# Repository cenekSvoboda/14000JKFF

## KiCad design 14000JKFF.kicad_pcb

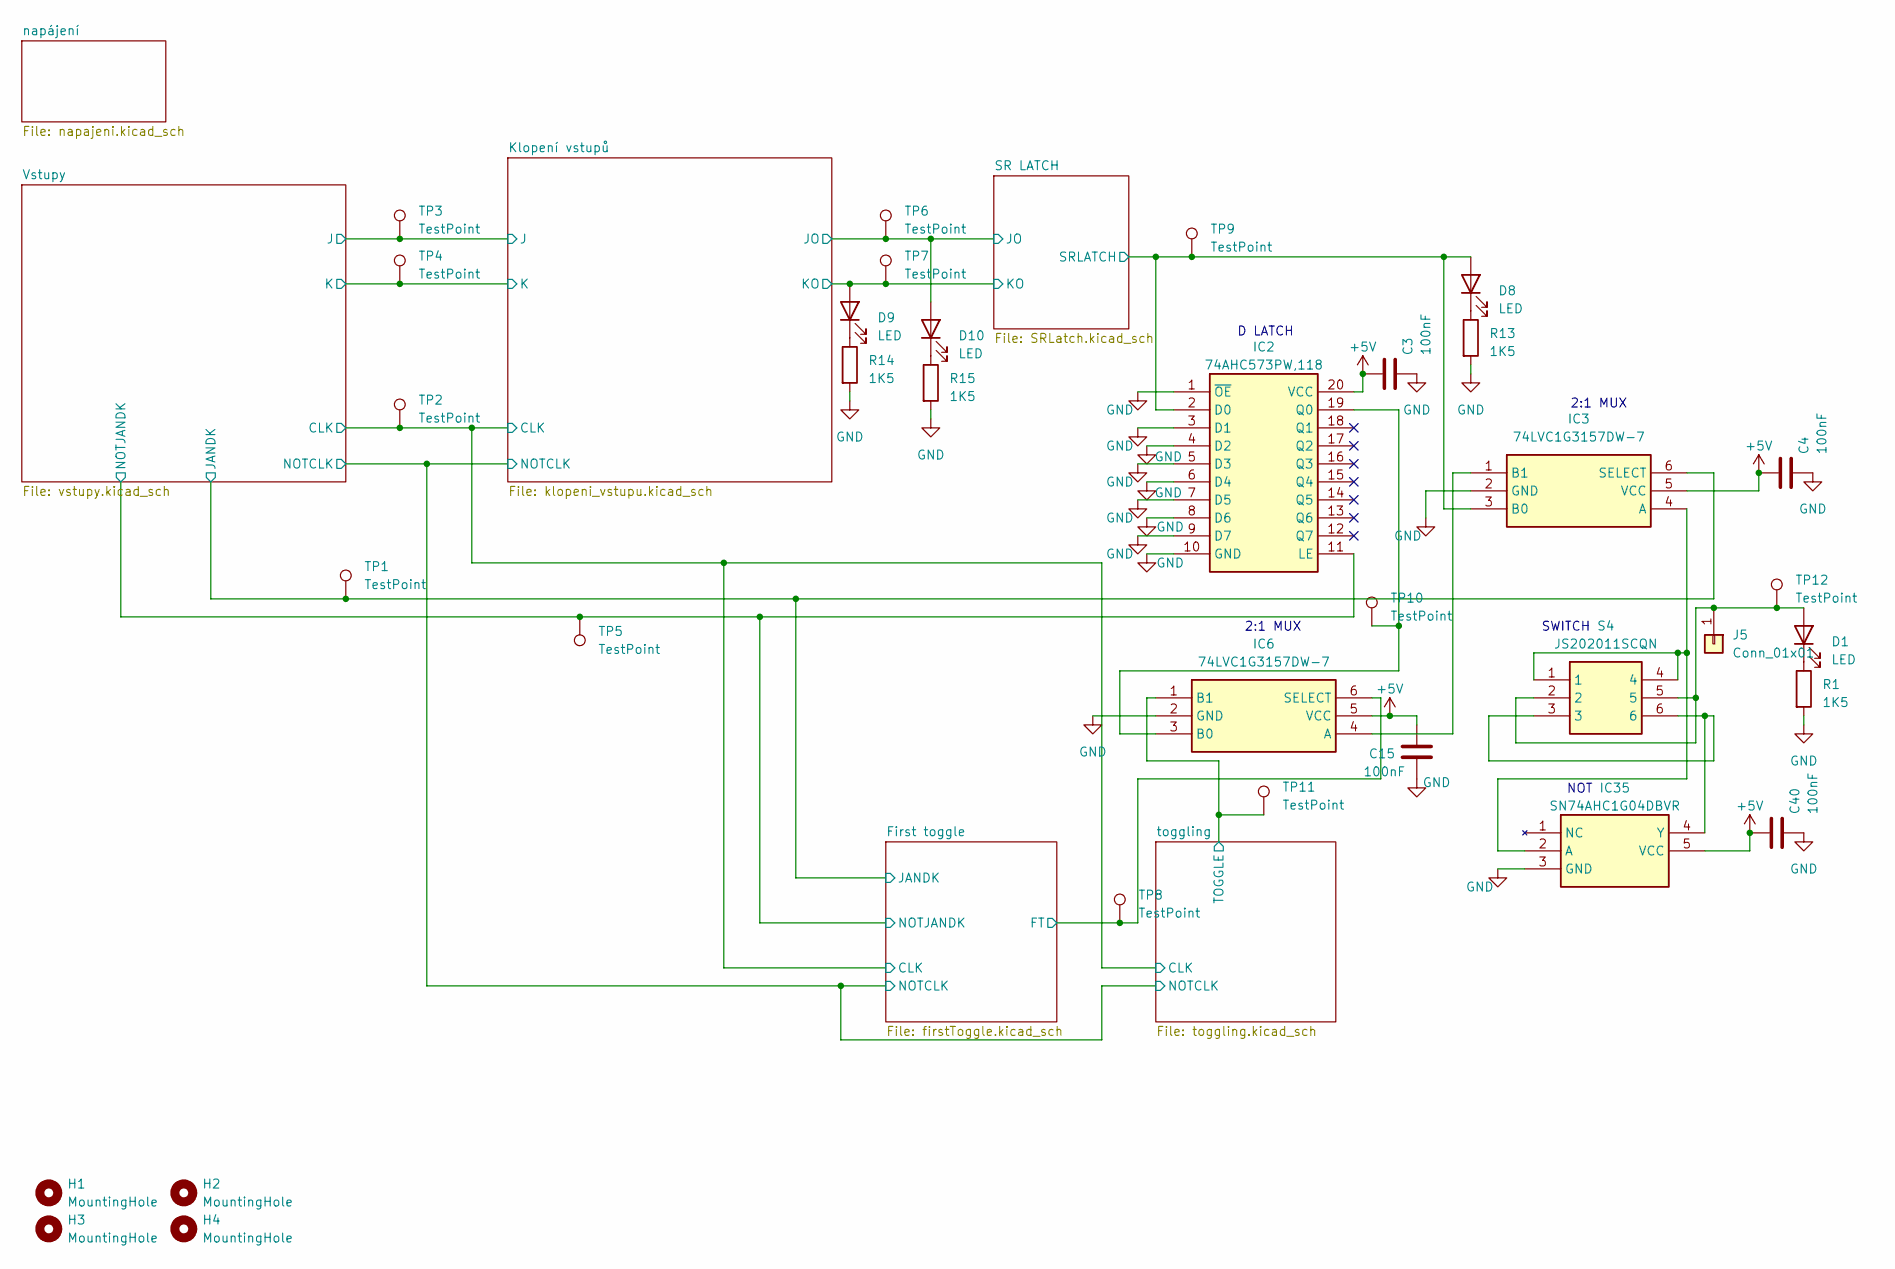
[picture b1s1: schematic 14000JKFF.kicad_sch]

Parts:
C3, C4, C15, C40: 100nF; C_1206_3216Metric
D1: LED; LED_D3.0mm
D8, D9, D10: LED; LED_1206_3216Metric
H1, H2, H3, H4: MountingHole; MountingHole_3.2mm_M3
IC2: 74AHC573PW,118; SOP65P640X110-20N; Manufacturer_Part_Number 74AHC573PW,118
IC3, IC6: 74LVC1G3157DW-7; SOT65P210X110-6N; Manufacturer_Part_Number 74LVC1G3157DW-7
IC35: SN74AHC1G04DBVR; SOT95P280X145-5N; Manufacturer_Part_Number SN74AHC1G04DBVR
J5: Conn_01x01; PinHeader_1x01_P2.54mm_Vertical
R1, R13, R14, R15: 1K5; R_1206_3216Metric
S4: JS202011SCQN; Manufacturer_Part_Number JS202011SCQN
TP1, TP2, TP3, TP4, TP5, TP6, TP7, TP8, TP9, TP10, TP11, TP12: TestPoint; TestPoint_Pad_1.5x1.5mm

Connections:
+5V: C3.2, C4.2, C15.2, C40.2, IC2.20 (VCC), IC3.5 (VCC), IC6.5 (VCC), IC35.5 (VCC); also elsewhere on the board
/First toggle/CLK: TP2.1; also elsewhere on the board
/First toggle/FT: IC6.6 (SELECT), TP8.1; also elsewhere on the board
/First toggle/JANDK: IC3.6 (SELECT), TP1.1; also elsewhere on the board
/First toggle/NOTJANDK: IC2.11 (LE), TP5.1; also elsewhere on the board
/Klopení vstupů/J: TP3.1; also elsewhere on the board
/Klopení vstupů/JO: D10.2 (A), TP6.1; also elsewhere on the board
/Klopení vstupů/K: TP4.1; also elsewhere on the board
/Klopení vstupů/KO: D9.2 (A), TP7.1; also elsewhere on the board
/SR LATCH/SRLATCH: D8.2 (A), IC2.2 (D0), IC3.3 (B0), TP9.1; also elsewhere on the board
/toggling/TOGGLE: IC6.1 (B1), TP11.1; also elsewhere on the board
GND: C3.1, C4.1, C15.1, C40.1, IC2.1 (~OE), IC2.3 (D1), IC2.4 (D2), IC2.5 (D3), IC2.6 (D4), IC2.7 (D5), IC2.8 (D6), IC2.9 (D7), IC2.10 (GND), IC3.2 (GND), IC6.2 (GND), IC35.3 (GND), R1.2, R13.2, R14.2, R15.2; also elsewhere on the board
unnamed: D1.2 (A), J5.1, S4.2, S4.5, TP12.1
unnamed: D1.1 (K), R1.1
unnamed: D8.1 (K), R13.1
unnamed: D9.1 (K), R14.1
unnamed: D10.1 (K), R15.1
unnamed: IC2.19 (Q0), IC6.3 (B0), TP10.1
unnamed: IC3.4 (A), IC35.2 (A), S4.1, S4.4
unnamed: IC3.1 (B1), IC6.4 (A)
unnamed: IC35.4 (Y), S4.3, S4.6

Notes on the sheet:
NOT
2:1 MUX
D LATCH
SWITCH

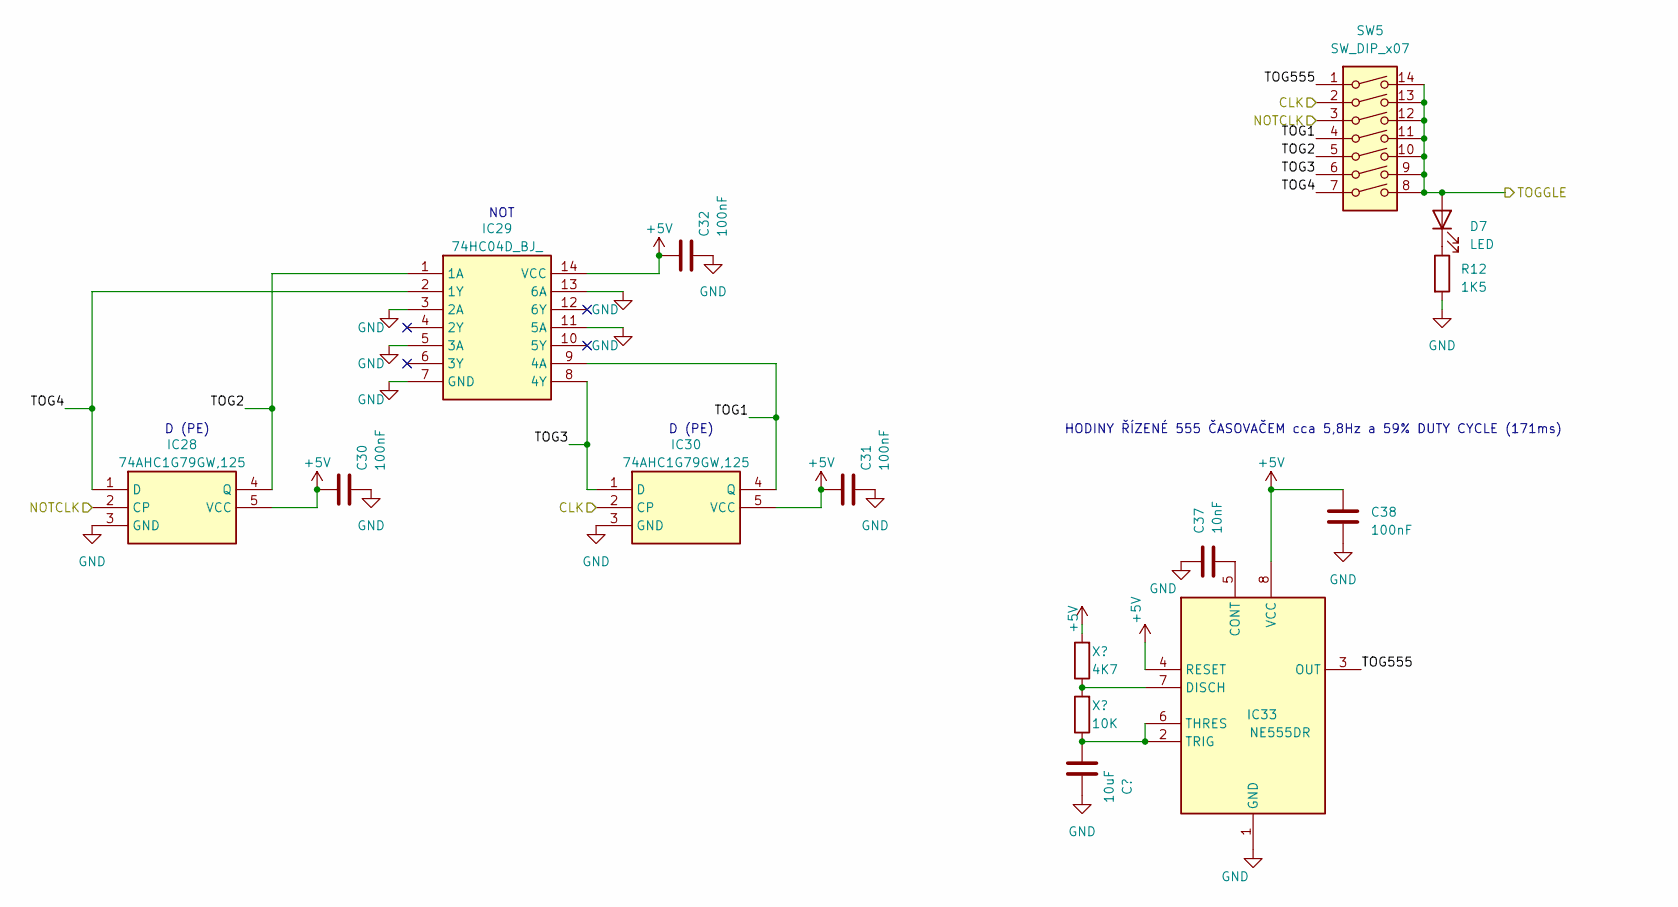
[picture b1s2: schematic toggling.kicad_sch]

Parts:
C30, C31, C32, C38: 100nF; C_1206_3216Metric
C36: 10uF; CP_Radial_D4.0mm_P2.00mm
C37: 10nF; C_1206_3216Metric
D7: LED; LED_1206_3216Metric
IC28, IC30: 74AHC1G79GW,125; SOT65P212X110-5N; Manufacturer_Part_Number 74AHC1G79GW,125
IC29: 74HC04D_BJ_; SOIC127P600X175-14N; Manufacturer_Part_Number 74HC04D(BJ)
IC33: NE555DR; SOIC127P600X175-8N; Manufacturer_Part_Number NE555DR
R12: 1K5; R_1206_3216Metric
SW5: SW_DIP_x07; DIP-14_W7.62mm
X1: 4K7; R_1206_3216Metric
X2: 10K; R_1206_3216Metric

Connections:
+5V: C30.2, C31.2, C32.2, C38.2, IC28.5 (VCC), IC29.14 (VCC), IC30.5 (VCC), IC33.4 (RESET), IC33.8 (VCC), X1.2; also elsewhere on the board
/First toggle/CLK: IC30.2 (CP), SW5.2; also elsewhere on the board
/First toggle/NOTCLK: IC28.2 (CP), SW5.3; also elsewhere on the board
/toggling/TOG1: IC29.9 (4A), IC30.4 (Q), SW5.4
/toggling/TOG2: IC28.4 (Q), IC29.1 (1A), SW5.5
/toggling/TOG3: IC29.8 (4Y), IC30.1 (D), SW5.6
/toggling/TOG4: IC28.1 (D), IC29.2 (1Y), SW5.7
/toggling/TOG555: IC33.3 (OUT), SW5.1
/toggling/TOGGLE: D7.2 (A), SW5.8, SW5.9, SW5.10, SW5.11, SW5.12, SW5.13, SW5.14; also elsewhere on the board
GND: C30.1, C31.1, C32.1, C36.1, C37.1, C38.1, IC28.3 (GND), IC29.3 (2A), IC29.5 (3A), IC29.7 (GND), IC29.11 (5A), IC29.13 (6A), IC30.3 (GND), IC33.1 (GND), R12.2; also elsewhere on the board
unnamed: D7.1 (K), R12.1
unnamed: C37.2, IC33.5 (CONT)
unnamed: IC33.7 (DISCH), X1.1, X2.2
unnamed: C36.2, IC33.2 (TRIG), IC33.6 (THRES), X2.1

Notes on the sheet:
NOT
D (PE)
HODINY ŘÍZENÉ 555 ČASOVAČEM cca 5,8Hz a 59% DUTY CYCLE (171ms)

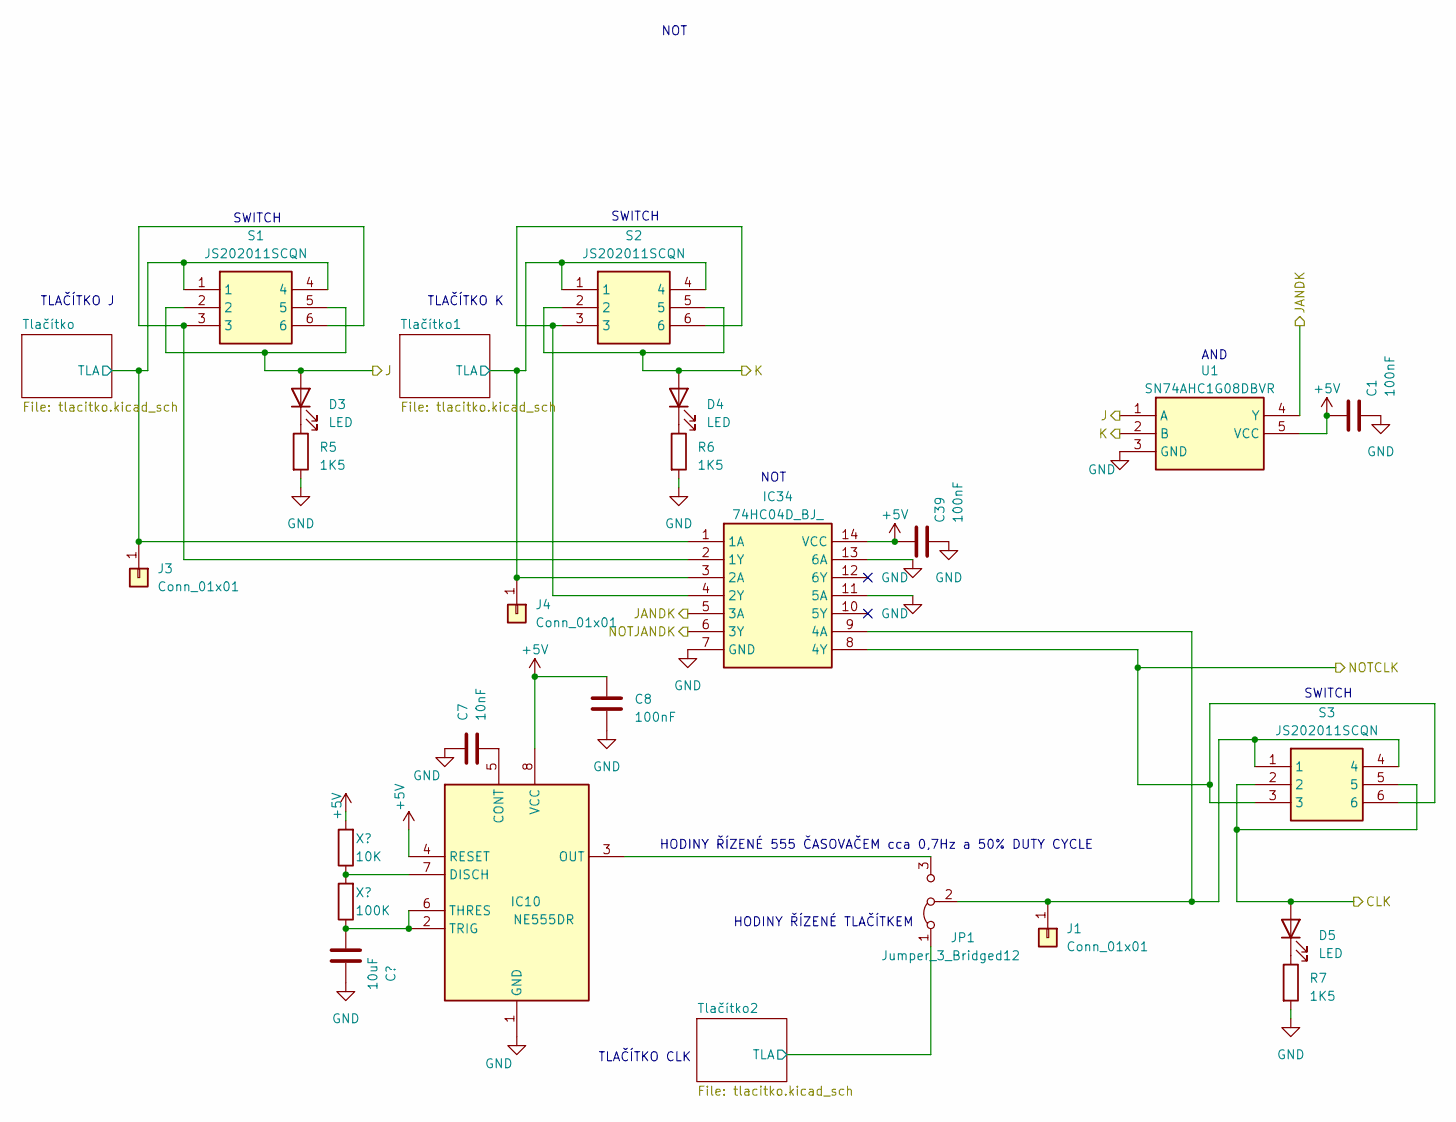
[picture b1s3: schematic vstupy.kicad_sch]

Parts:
C1, C8, C39: 100nF; C_1206_3216Metric
C6: 10uF; CP_Radial_D4.0mm_P2.00mm
C7: 10nF; C_1206_3216Metric
D3, D4, D5: LED; LED_1206_3216Metric
IC10: NE555DR; SOIC127P600X175-8N; Manufacturer_Part_Number NE555DR
IC34: 74HC04D_BJ_; SOIC127P600X175-14N; Manufacturer_Part_Number 74HC04D(BJ)
J1, J3, J4: Conn_01x01; PinHeader_1x01_P2.54mm_Vertical
JP1: Jumper_3_Bridged12; PinHeader_1x03_P2.54mm_Vertical
R3: 10K; R_1206_3216Metric
R4: 100K; R_1206_3216Metric
R5, R6, R7: 1K5; R_1206_3216Metric
S1, S2, S3: JS202011SCQN; Manufacturer_Part_Number JS202011SCQN
U1: SN74AHC1G08DBVR; SOT95P280X145-5N; Manufacturer_Part_Number SN74AHC1G08DBVR

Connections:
+5V: C1.2, C8.2, C39.2, IC10.4 (RESET), IC10.8 (VCC), IC34.14 (VCC), R3.2, U1.5 (VCC); also elsewhere on the board
/First toggle/CLK: D5.2 (A), S3.2, S3.5; also elsewhere on the board
/First toggle/JANDK: IC34.5 (3A), U1.4 (Y); also elsewhere on the board
/First toggle/NOTCLK: IC34.8 (4Y), S3.3, S3.6; also elsewhere on the board
/First toggle/NOTJANDK: IC34.6 (3Y); also elsewhere on the board
/Klopení vstupů/J: D3.2 (A), S1.2, S1.5, U1.1 (A); also elsewhere on the board
/Klopení vstupů/K: D4.2 (A), S2.2, S2.5, U1.2 (B); also elsewhere on the board
/Vstupy/Tlačítko1/TLA: IC34.3 (2A), J4.1, S2.1, S2.4; also elsewhere on the board
/Vstupy/Tlačítko2/TLA: JP1.1 (A); also elsewhere on the board
/Vstupy/Tlačítko/TLA: IC34.1 (1A), J3.1, S1.1, S1.4; also elsewhere on the board
GND: C1.1, C6.1, C7.1, C8.1, C39.1, IC10.1 (GND), IC34.7 (GND), IC34.11 (5A), IC34.13 (6A), R5.2, R6.2, R7.2, U1.3 (GND); also elsewhere on the board
unnamed: D3.1 (K), R5.1
unnamed: D4.1 (K), R6.1
unnamed: D5.1 (K), R7.1
unnamed: C7.2, IC10.5 (CONT)
unnamed: IC10.7 (DISCH), R3.1, R4.2
unnamed: IC10.3 (OUT), JP1.3 (B)
unnamed: C6.2, IC10.2 (TRIG), IC10.6 (THRES), R4.1
unnamed: IC34.2 (1Y), S1.3, S1.6
unnamed: IC34.4 (2Y), S2.3, S2.6
unnamed: IC34.9 (4A), J1.1, JP1.2 (C), S3.1, S3.4

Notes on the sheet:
HODINY ŘÍZENÉ 555 ČASOVAČEM cca 0,7Hz a 50% DUTY CYCLE
SWITCH
NOT
TLAČÍTKO K
HODINY ŘÍZENÉ TLAČÍTKEM
AND
TLAČÍTKO J
TLAČÍTKO CLK

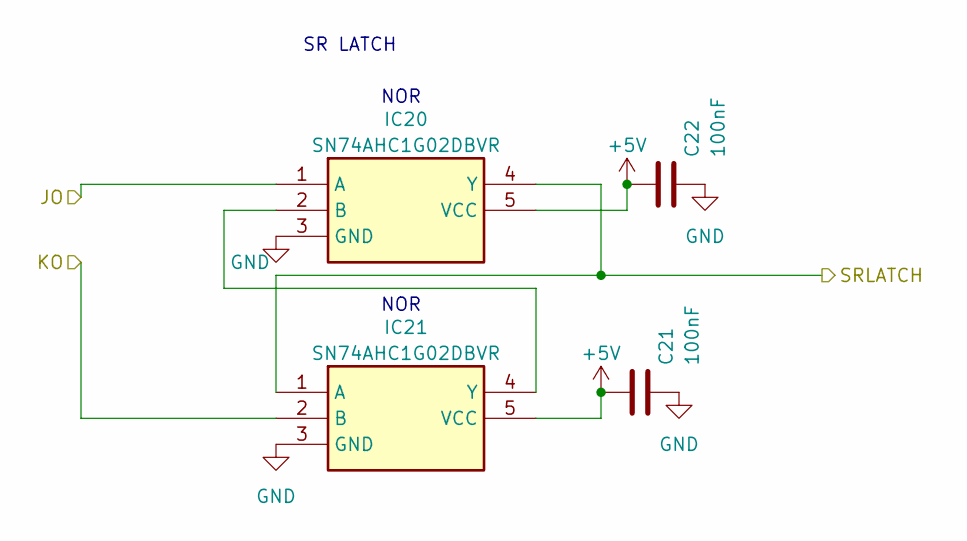
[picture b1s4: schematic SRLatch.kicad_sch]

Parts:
C21, C22: 100nF; C_1206_3216Metric
IC20, IC21: SN74AHC1G02DBVR; SOT95P280X145-5N; Manufacturer_Part_Number SN74AHC1G02DBVR

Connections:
+5V: C21.2, C22.2, IC20.5 (VCC), IC21.5 (VCC); also elsewhere on the board
/Klopení vstupů/JO: IC20.1 (A); also elsewhere on the board
/Klopení vstupů/KO: IC21.2 (B); also elsewhere on the board
/SR LATCH/SRLATCH: IC20.4 (Y), IC21.1 (A); also elsewhere on the board
GND: C21.1, C22.1, IC20.3 (GND), IC21.3 (GND); also elsewhere on the board
unnamed: IC20.2 (B), IC21.4 (Y)

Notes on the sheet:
NOR
SR LATCH

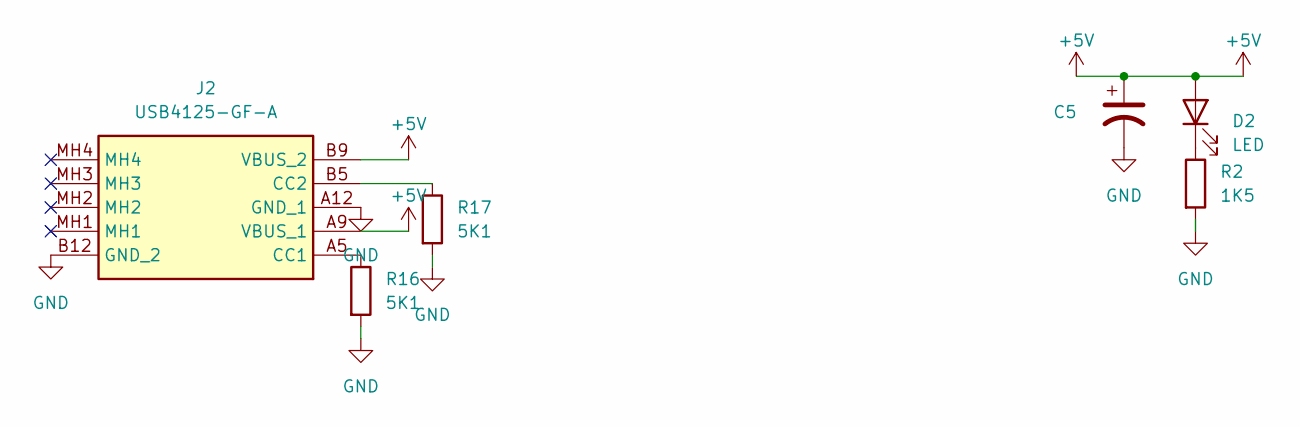
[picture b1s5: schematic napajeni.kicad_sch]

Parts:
C5: 293D106X96R3A2TE3; CAPMP3216X180N
D2: LED; LED_1206_3216Metric
J2: USB4125-GF-A; USB4125GFA; Manufacturer_Part_Number USB4125-GF-A
R2: 1K5; R_1206_3216Metric
R16, R17: 5K1; R_1206_3216Metric

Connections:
+5V: C5.1, D2.2 (A), J2.A9 (VBUS_1), J2.B9 (VBUS_2); also elsewhere on the board
GND: C5.2, J2.A12 (GND_1), J2.B12 (GND_2), R2.2, R16.2, R17.2; also elsewhere on the board
unnamed: D2.1 (K), R2.1
unnamed: J2.A5 (CC1), R16.1
unnamed: J2.B5 (CC2), R17.1

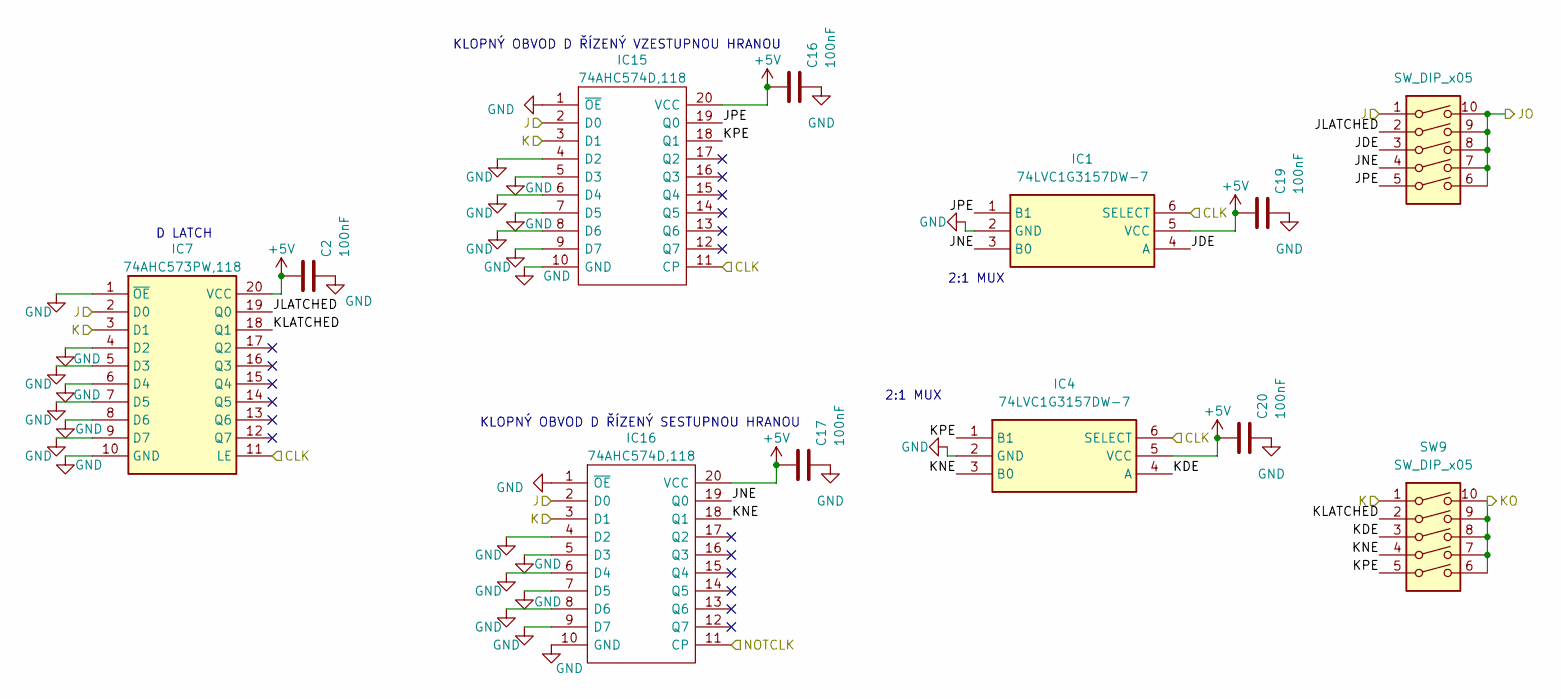
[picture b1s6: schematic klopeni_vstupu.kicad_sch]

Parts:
C2, C16, C17, C19, C20: 100nF; C_1206_3216Metric
IC1, IC4: 74LVC1G3157DW-7; SOT65P210X110-6N; Manufacturer_Part_Number 74LVC1G3157DW-7
IC7: 74AHC573PW,118; SOP65P640X110-20N; Manufacturer_Part_Number 74AHC573PW,118
IC15, IC16: 74AHC574D,118; SOIC127P1032X265-20N; Manufacturer_Part_Number 74AHC574D,118
SW8, SW9: SW_DIP_x05; DIP-10_W7.62mm

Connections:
+5V: C2.2, C16.2, C17.2, C19.2, C20.2, IC1.5 (VCC), IC4.5 (VCC), IC7.20 (VCC), IC15.20 (VCC), IC16.20 (VCC); also elsewhere on the board
/First toggle/CLK: IC1.6 (SELECT), IC4.6 (SELECT), IC7.11 (LE), IC15.11 (CP); also elsewhere on the board
/First toggle/NOTCLK: IC16.11 (CP); also elsewhere on the board
/Klopení vstupů/J: IC7.2 (D0), IC15.2 (D0), IC16.2 (D0), SW8.1; also elsewhere on the board
/Klopení vstupů/JDE: IC1.4 (A), SW8.3
/Klopení vstupů/JLATCHED: IC7.19 (Q0), SW8.2
/Klopení vstupů/JNE: IC1.3 (B0), IC16.19 (Q0), SW8.4
/Klopení vstupů/JO: SW8.6, SW8.7, SW8.8, SW8.9, SW8.10; also elsewhere on the board
/Klopení vstupů/JPE: IC1.1 (B1), IC15.19 (Q0), SW8.5
/Klopení vstupů/K: IC7.3 (D1), IC15.3 (D1), IC16.3 (D1), SW9.1; also elsewhere on the board
/Klopení vstupů/KDE: IC4.4 (A), SW9.3
/Klopení vstupů/KLATCHED: IC7.18 (Q1), SW9.2
/Klopení vstupů/KNE: IC4.3 (B0), IC16.18 (Q1), SW9.4
/Klopení vstupů/KO: SW9.6, SW9.7, SW9.8, SW9.9, SW9.10; also elsewhere on the board
/Klopení vstupů/KPE: IC4.1 (B1), IC15.18 (Q1), SW9.5
GND: C2.1, C16.1, C17.1, C19.1, C20.1, IC1.2 (GND), IC4.2 (GND), IC7.1 (~OE), IC7.4 (D2), IC7.5 (D3), IC7.6 (D4), IC7.7 (D5), IC7.8 (D6), IC7.9 (D7), IC7.10 (GND), IC15.1 (~OE), IC15.4 (D2), IC15.5 (D3), IC15.6 (D4), IC15.7 (D5), IC15.8 (D6), IC15.9 (D7), IC15.10 (GND), IC16.1 (~OE), IC16.4 (D2), IC16.5 (D3), IC16.6 (D4), IC16.7 (D5), IC16.8 (D6), IC16.9 (D7), IC16.10 (GND); also elsewhere on the board

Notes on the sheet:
KLOPNÝ OBVOD D ŘÍZENÝ VZESTUPNOU HRANOU
2:1 MUX
KLOPNÝ OBVOD D ŘÍZENÝ SESTUPNOU HRANOU
D LATCH

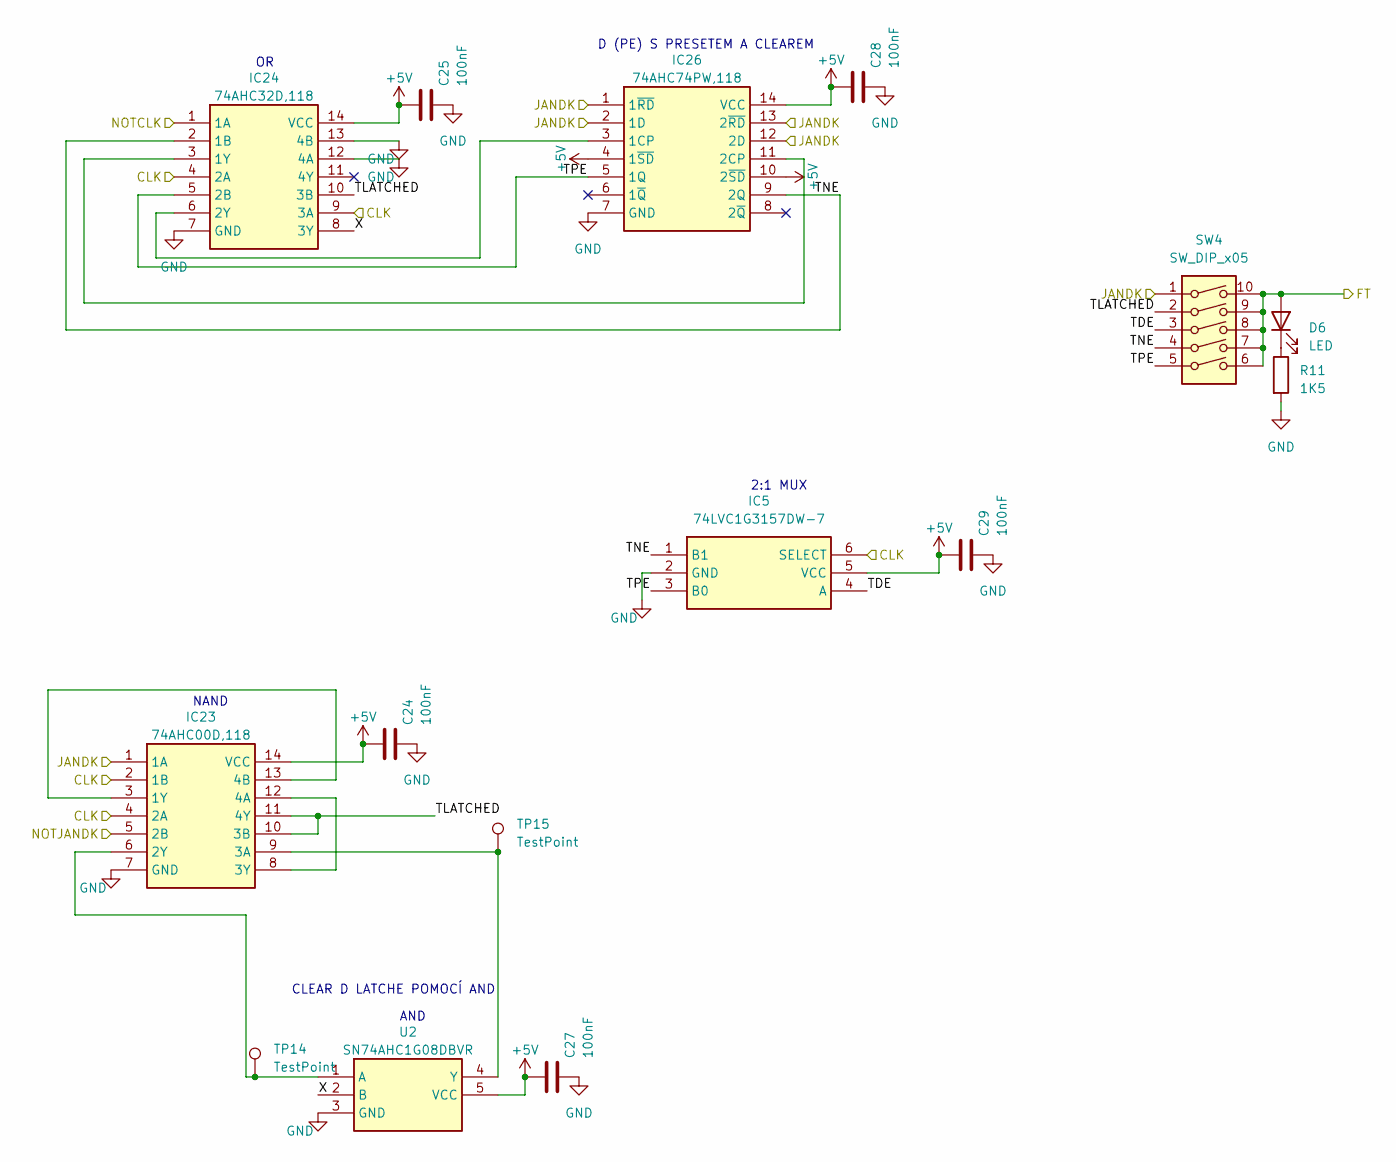
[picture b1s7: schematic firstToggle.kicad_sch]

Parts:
C24, C25, C27, C28, C29: 100nF; C_1206_3216Metric
D6: LED; LED_1206_3216Metric
IC5: 74LVC1G3157DW-7; SOT65P210X110-6N; Manufacturer_Part_Number 74LVC1G3157DW-7
IC23: 74AHC00D,118; SOIC127P600X175-14N; Manufacturer_Part_Number 74AHC00D,118
IC24: 74AHC32D,118; SOIC127P600X175-14N; Manufacturer_Part_Number 74AHC32D,118
IC26: 74AHC74PW,118; SOP65P640X110-14N; Manufacturer_Part_Number 74AHC74PW,118
R11: 1K5; R_1206_3216Metric
SW4: SW_DIP_x05; DIP-10_W7.62mm
TP14, TP15: TestPoint; TestPoint_Pad_1.5x1.5mm
U2: SN74AHC1G08DBVR; SOT95P280X145-5N; Manufacturer_Part_Number SN74AHC1G08DBVR

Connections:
+5V: C24.2, C25.2, C27.2, C28.2, C29.2, IC5.5 (VCC), IC23.14 (VCC), IC24.14 (VCC), IC26.4 (1~SD), IC26.10 (2~SD), IC26.14 (VCC), U2.5 (VCC); also elsewhere on the board
/First toggle/CLK: IC5.6 (SELECT), IC23.2 (1B), IC23.4 (2A), IC24.4 (2A), IC24.9 (3A); also elsewhere on the board
/First toggle/FT: D6.2 (A), SW4.6, SW4.7, SW4.8, SW4.9, SW4.10; also elsewhere on the board
/First toggle/JANDK: IC23.1 (1A), IC26.1 (1~RD), IC26.2 (1D), IC26.12 (2D), IC26.13 (2~RD), SW4.1; also elsewhere on the board
/First toggle/NOTCLK: IC24.1 (1A); also elsewhere on the board
/First toggle/NOTJANDK: IC23.5 (2B); also elsewhere on the board
/First toggle/TDE: IC5.4 (A), SW4.3
/First toggle/TLATCHED: IC23.10 (3B), IC23.11 (4Y), IC24.10 (3B), SW4.2
/First toggle/TNE: IC5.1 (B1), IC24.2 (1B), IC26.9 (2Q), SW4.4
/First toggle/TPE: IC5.3 (B0), IC24.5 (2B), IC26.5 (1Q), SW4.5
/First toggle/X: IC24.8 (3Y), U2.2 (B)
GND: C24.1, C25.1, C27.1, C28.1, C29.1, IC5.2 (GND), IC23.7 (GND), IC24.7 (GND), IC24.12 (4A), IC24.13 (4B), IC26.7 (GND), R11.2, U2.3 (GND); also elsewhere on the board
unnamed: D6.1 (K), R11.1
unnamed: IC23.3 (1Y), IC23.13 (4B)
unnamed: IC23.6 (2Y), TP14.1, U2.1 (A)
unnamed: IC23.9 (3A), TP15.1, U2.4 (Y)
unnamed: IC23.8 (3Y), IC23.12 (4A)
unnamed: IC24.3 (1Y), IC26.11 (2CP)
unnamed: IC24.6 (2Y), IC26.3 (1CP)

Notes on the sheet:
NAND
D (PE) S PRESETEM A CLEAREM
AND
2:1 MUX
CLEAR D LATCHE POMOCÍ AND

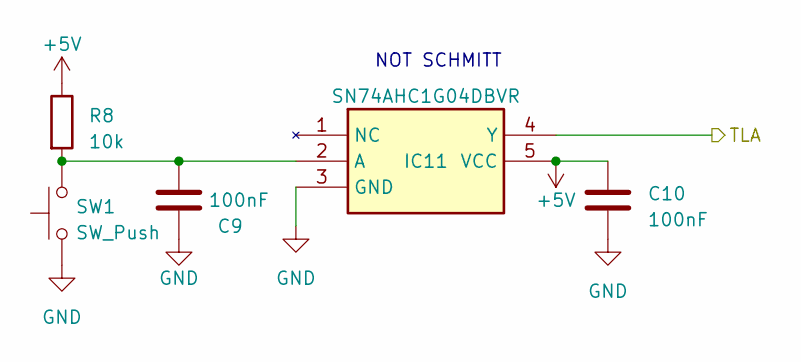
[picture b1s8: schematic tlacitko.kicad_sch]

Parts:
C9, C10: 100nF; C_1206_3216Metric
IC11: SN74AHC1G04DBVR; SOT95P280X145-5N; Manufacturer_Part_Number SN74AHC1G04DBVR
R8: 10k; R_1206_3216Metric
SW1: SW_Push; SW_PUSH_6mm_H7.3mm

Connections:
+5V: C10.2, IC11.5 (VCC), R8.1; also elsewhere on the board
/Vstupy/Tlačítko/TLA: IC11.4 (Y); also elsewhere on the board
GND: C9.1, C10.1, IC11.3 (GND), SW1.1; also elsewhere on the board
unnamed: C9.2, IC11.2 (A), R8.2, SW1.2

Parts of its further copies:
C11, C12, C13, C14: 100nF; C_1206_3216Metric
IC12, IC13: SN74AHC1G04DBVR; SOT95P280X145-5N; Manufacturer_Part_Number SN74AHC1G04DBVR
R9, R10: 10k; R_1206_3216Metric
SW2, SW3: SW_Push; SW_PUSH_6mm_H7.3mm

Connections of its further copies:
+5V: C12.2, C14.2, IC12.5 (VCC), IC13.5 (VCC), R9.1, R10.1; also elsewhere on the board
/Vstupy/Tlačítko1/TLA: IC12.4 (Y); also elsewhere on the board
/Vstupy/Tlačítko2/TLA: IC13.4 (Y); also elsewhere on the board
GND: C11.1, C12.1, C13.1, C14.1, IC12.3 (GND), IC13.3 (GND), SW2.1, SW3.1; also elsewhere on the board
unnamed: C11.2, IC12.2 (A), R9.2, SW2.2
unnamed: C13.2, IC13.2 (A), R10.2, SW3.2

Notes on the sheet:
NOT SCHMITT

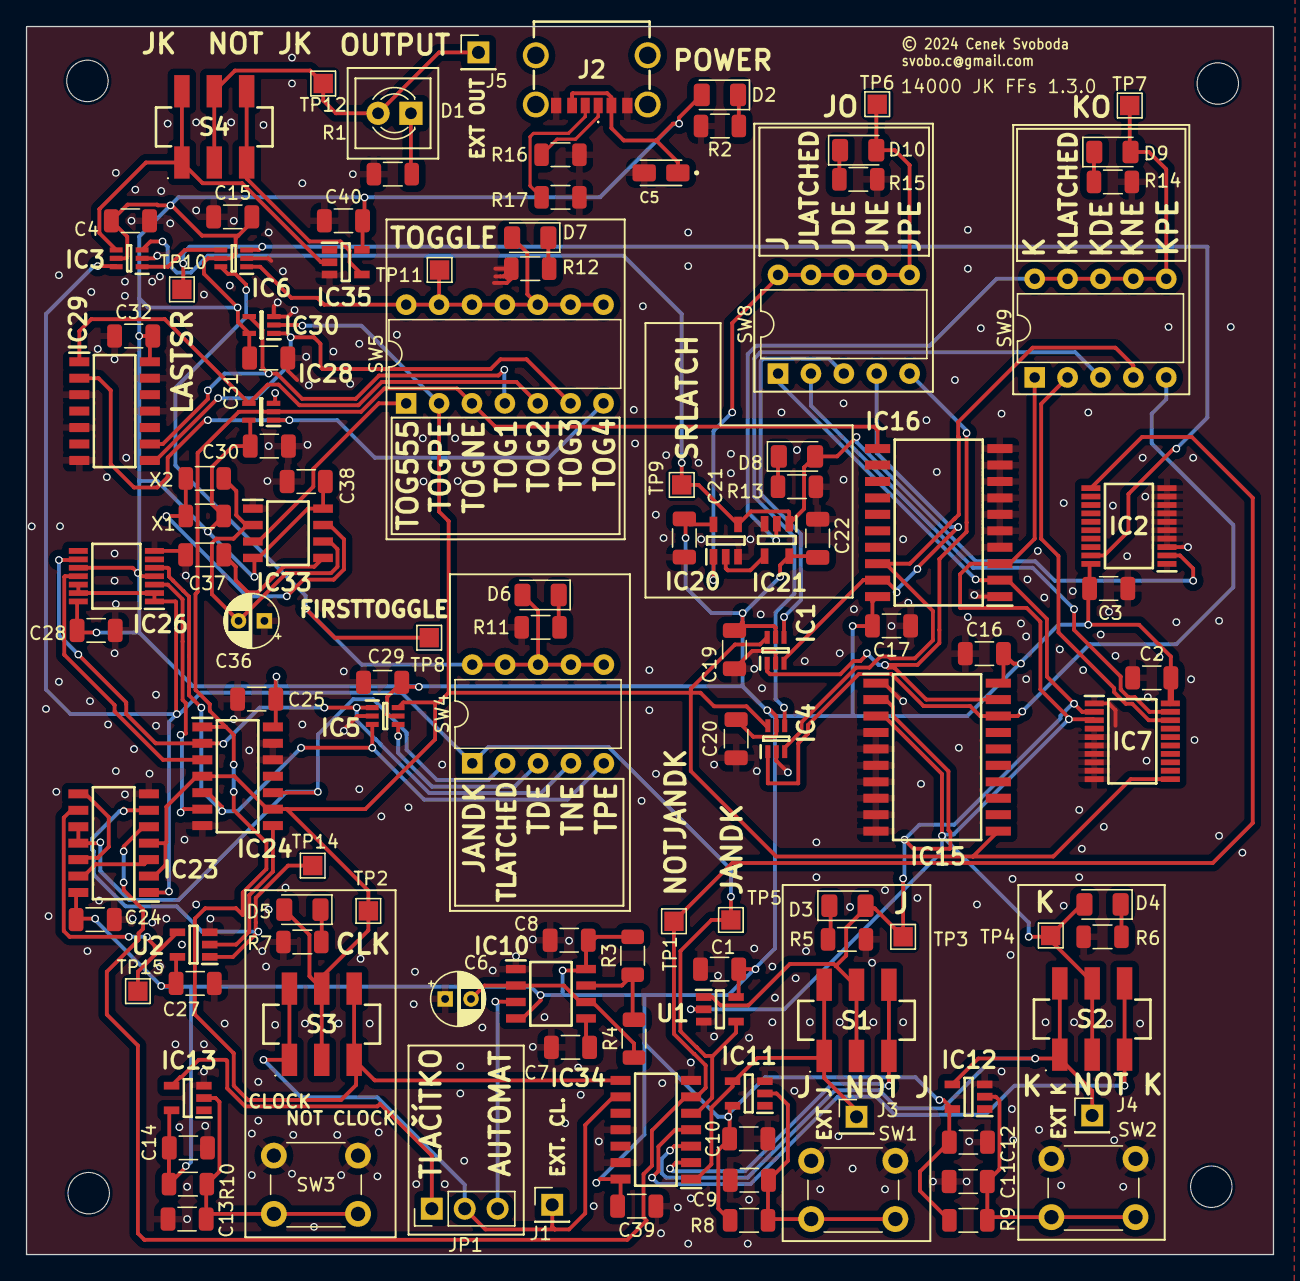
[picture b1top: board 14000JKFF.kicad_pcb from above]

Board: 2 copper layers, 96.3 x 94.8 mm, 124 parts (0 on the bottom side), 71 nets.

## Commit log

2024-04-18 14000JKFF 1.1.0
2024-04-27 promo 1.2.0
2024-05-08 promo 1.3
2024-05-08 version 1.3
2024-05-08 Update LICENSE
2024-05-19 fix pdf

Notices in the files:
14000JKFF.kicad_pcb:
© 2024 Cenek Svoboda
